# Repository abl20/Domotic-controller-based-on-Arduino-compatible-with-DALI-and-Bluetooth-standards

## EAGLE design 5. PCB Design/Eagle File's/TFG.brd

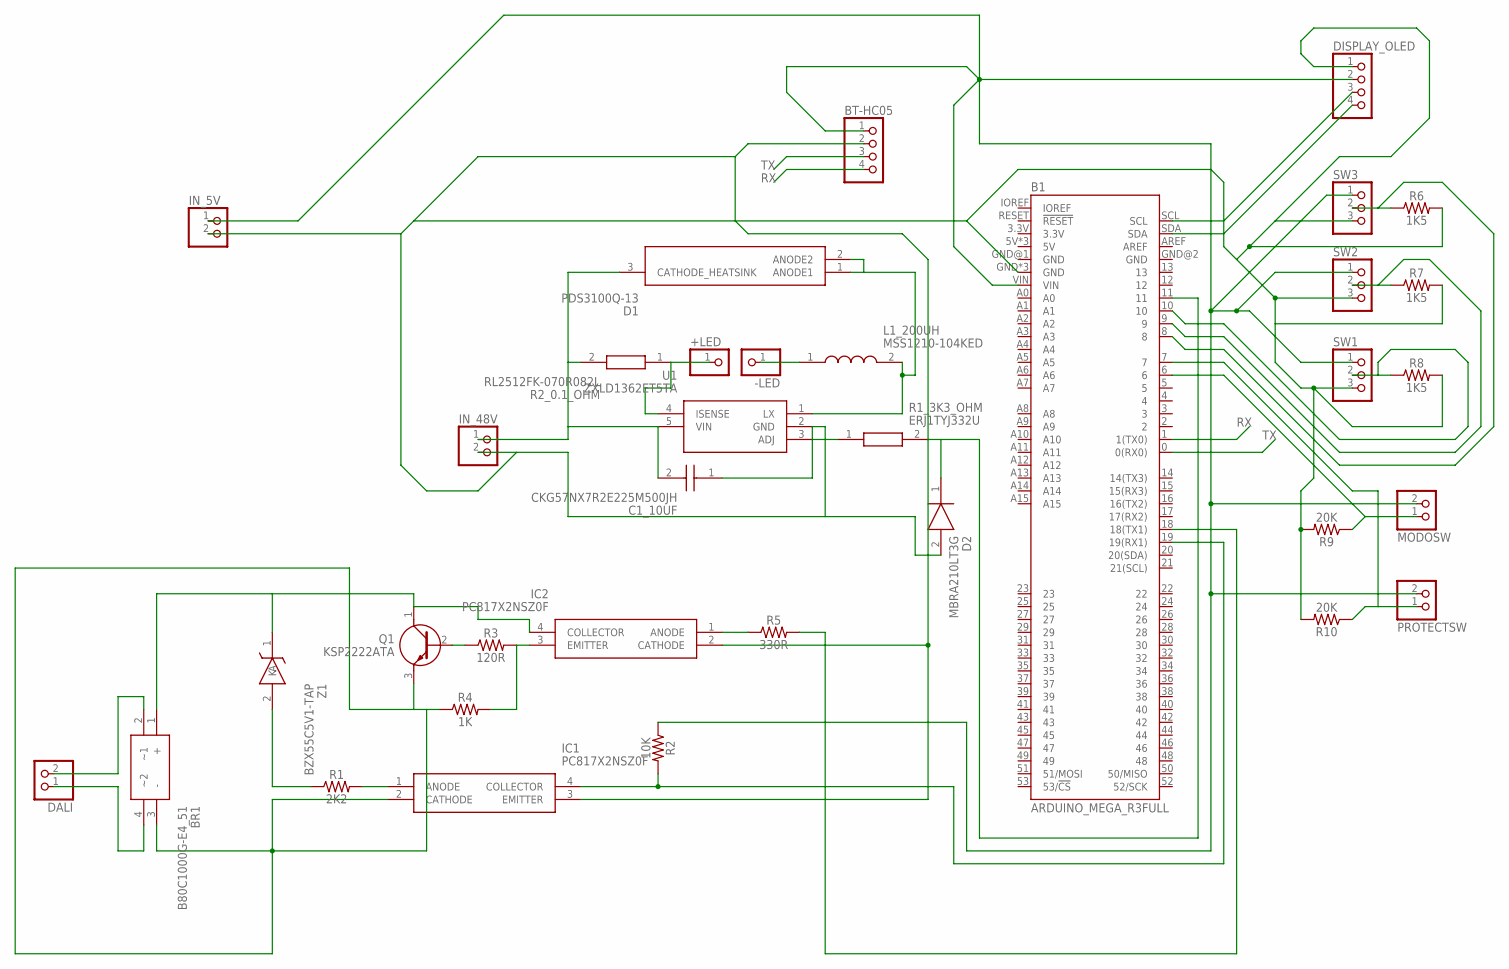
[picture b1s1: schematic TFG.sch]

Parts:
+LED: PINHD-1X1; 1X01
-LED: PINHD-1X1; 1X01
B1: ARDUINO_MEGA_R3FULL; ARDUINO_MEGA_NO_SILK
BR1: B80C1000G-E4_51; WOG_1
BT-HC05: PINHD-1X4; 1X04
C1_10UF: CKG57NX7R2E225M500JH; CAPC6050X550N
D1: PDS3100Q-13; POWERDI5
D2: MBRA210LT3G; DIOM5226X220N
DALI: PINHD-1X2; 1X02
DISPLAY_OLED: PINHD-1X4; 1X04
IC1, IC2: PC817X2NSZ0F; DIP762W60P254L458H400Q4N
IN_5V, IN_48V: PINHD-1X2; 1X02
L1_200UH: MSS1210-104KED; INDPM120120X1020N
MODOSW: PINHD-1X2; 1X02
PROTECTSW: PINHD-1X2; 1X02
Q1: KSP2222ATA; TO-92_FAIRCHILD
R1: 2K2; AXIAL-0.3
R1_3K3_OHM: ERJ1TYJ332U; RESC6432X70N
R2: 10K; AXIAL-0.3
R2_0.1_OHM: RL2512FK-070R082L; RESC6432X65N
R3: 120R; AXIAL-0.3
R4: 1K; AXIAL-0.3
R5: 330R; AXIAL-0.3
R6, R7, R8: 1K5; AXIAL-0.3
R9, R10: 20K; AXIAL-0.3
SW1, SW2, SW3: PINHD-1X3; 1X03
U1: ZXLD1362ET5TA; SOT95P270X145-5N
Z1: BZX55C5V1-TAP; DIOAD950W60L350D150

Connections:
2: C1_10UF.2, D1.3 (CATHODE_HEATSINK), IN_48V.1, R2_0.1_OHM.2, U1.5 (VIN)
unnamed: D1.1 (ANODE1), D1.2 (ANODE2), L1_200UH.2, U1.1 (LX)
unnamed: B1.GND, B1.GND@3 (GND), B1.GND@4 (GND), BT-HC05.2, C1_10UF.1, D2.2 (A), DISPLAY_OLED.1, IC1.3 (EMITTER), IC2.2 (CATHODE), IN_5V.2, IN_48V.2, R6.P$2 (2), R7.P$2 (2), R8.P$2 (2), R9.P$2 (2), R10.P$2 (2), SW1.3, SW2.3, SW3.3, U1.2 (GND)
unnamed: -LED.1, L1_200UH.1
unnamed: +LED.1, R2_0.1_OHM.1, U1.4 (ISENSE)
unnamed: B1.9, R7.P$1 (1), SW2.2
unnamed: B1.10, R8.P$1 (1), SW1.2
unnamed: B1.8, R6.P$1 (1), SW3.2
unnamed: R1_3K3_OHM.1, U1.3 (ADJ)
unnamed: B1.11, D2.1 (K), R1_3K3_OHM.2
unnamed: BR1.2 (~1), DALI.2
unnamed: BR1.4 (~2), DALI.1
unnamed: B1.6, MODOSW.1, R9.P$1 (1)
unnamed: BR1.1 (+), IC2.4 (COLLECTOR), Q1.1 (C), Z1.1 (K)
unnamed: R1.P$1 (1), Z1.2 (A)
unnamed: IC1.1 (ANODE), R1.P$2 (2)
unnamed: B1.19 (19(RX1)), IC1.4 (COLLECTOR), R2.P$2 (2)
unnamed: B1.VIN, BT-HC05.1, DISPLAY_OLED.2, IN_5V.1, MODOSW.2, PROTECTSW.2, R2.P$1 (1), SW1.1, SW2.1, SW3.1
unnamed: IC2.3 (EMITTER), R3.P$2 (2), R4.P$2 (2)
unnamed: Q1.2 (B), R3.P$1 (1)
unnamed: BR1.3 (-), IC1.2 (CATHODE), Q1.3 (E), R4.P$1 (1)
unnamed: B1.18 (18(TX1)), R5.P$2 (2)
unnamed: IC2.1 (ANODE), R5.P$1 (1)
unnamed: B1.7, PROTECTSW.1, R10.P$1 (1)
unnamed: B1.SCL, DISPLAY_OLED.3
unnamed: B1.SDA, DISPLAY_OLED.4
RX: B1.1 (1(TX0)), BT-HC05.4
TX: B1.0 (0(RX0)), BT-HC05.3

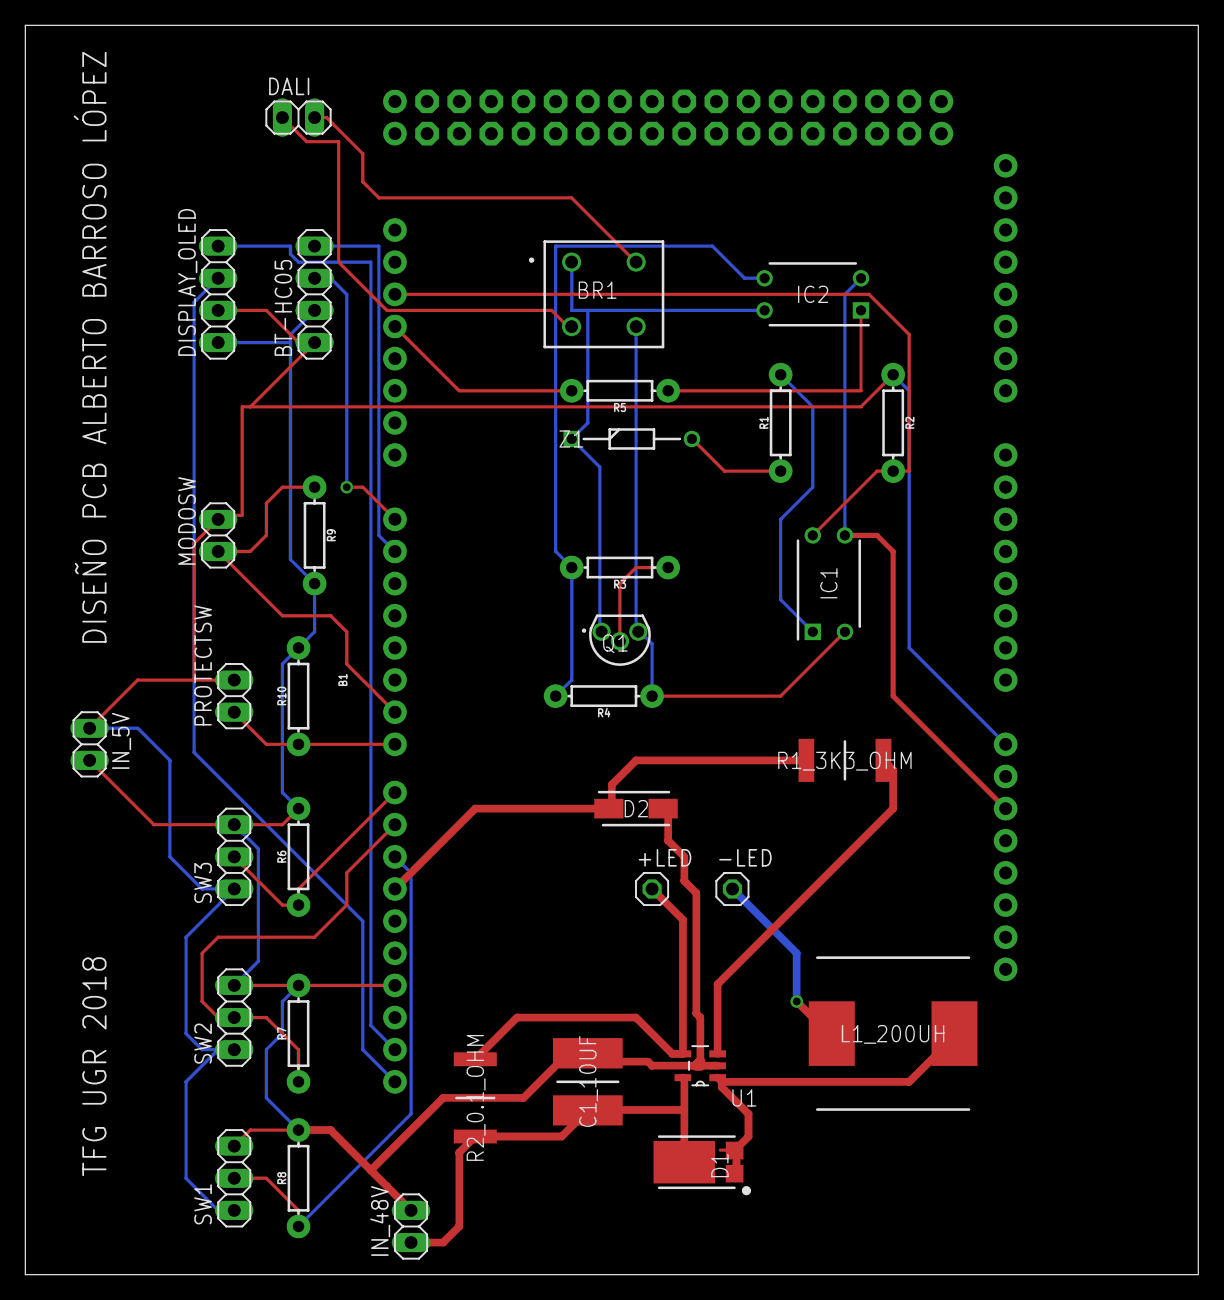
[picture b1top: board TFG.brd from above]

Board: 2 copper layers, 92.7 x 98.7 mm, 35 parts (0 on the bottom side), 28 nets.

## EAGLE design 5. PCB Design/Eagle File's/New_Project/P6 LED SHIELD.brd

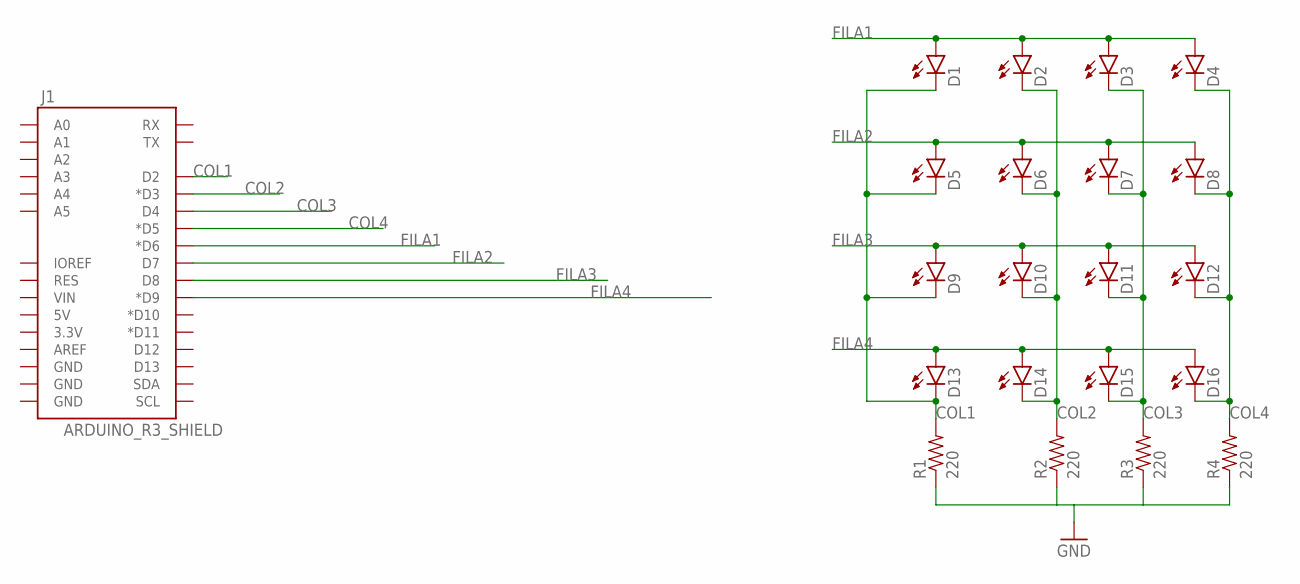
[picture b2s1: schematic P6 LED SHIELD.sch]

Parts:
D1, D2, D3, D4, D5, D6, D7, D8, D9, D10, D11, D12, D13, D14, D15, D16: LED5MM
J1: ARDUINO_R3_SHIELD; UNO_R3_SHIELD
R1, R2, R3, R4: 220; AXIAL-0.4

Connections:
COL1: D1.K (C), D5.K (C), D9.K (C), D13.K (C), J1.D2, R1.P$2 (2)
COL2: D2.K (C), D6.K (C), D10.K (C), D14.K (C), J1.D3 (*D3), R2.P$2 (2)
COL3: D3.K (C), D7.K (C), D11.K (C), D15.K (C), J1.D4, R3.P$2 (2)
COL4: D4.K (C), D8.K (C), D12.K (C), D16.K (C), J1.D5 (*D5), R4.P$2 (2)
FILA1: D1.A, D2.A, D3.A, D4.A, J1.D6 (*D6)
FILA2: D5.A, D6.A, D7.A, D8.A, J1.D7
FILA3: D9.A, D10.A, D11.A, D12.A, J1.D8
FILA4: D13.A, D14.A, D15.A, D16.A, J1.D9 (*D9)
GND: R1.P$1 (1), R2.P$1 (1), R3.P$1 (1), R4.P$1 (1)

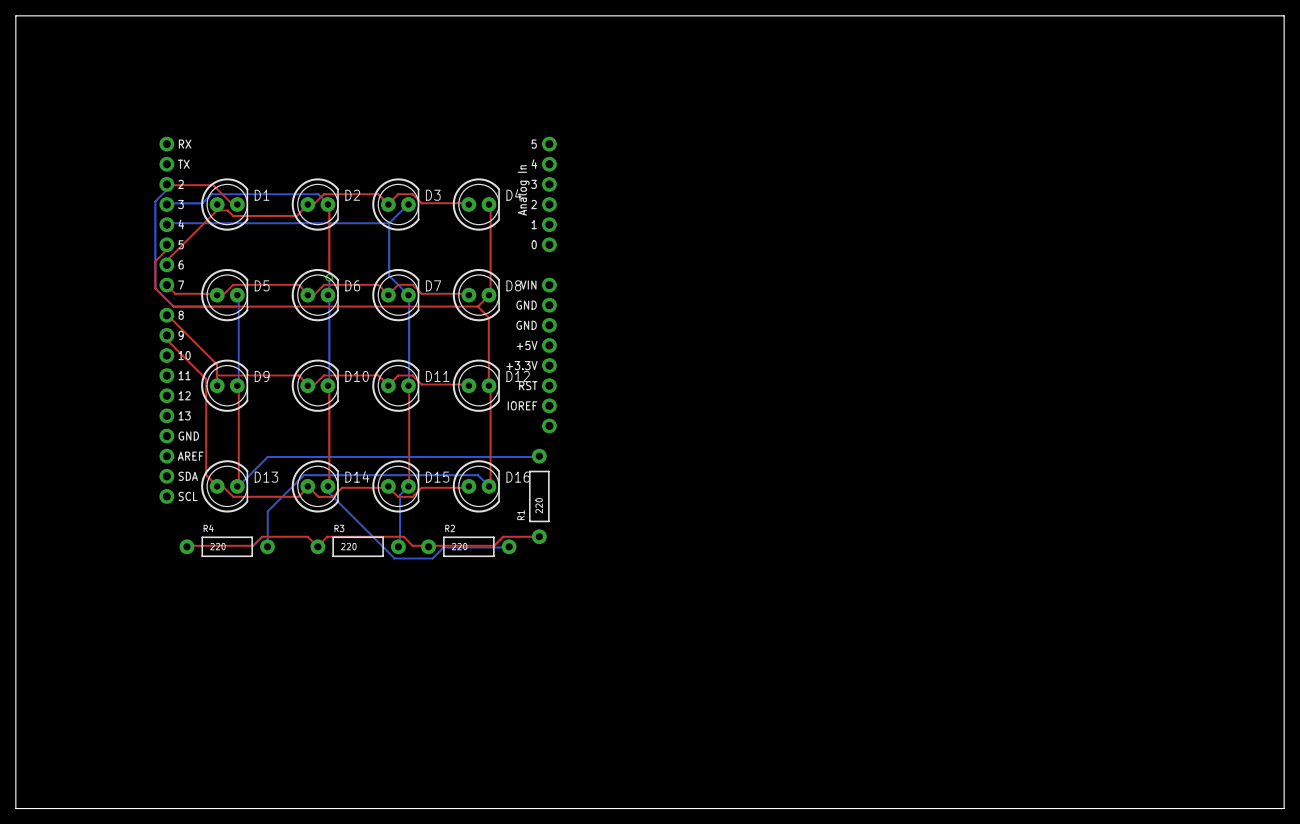
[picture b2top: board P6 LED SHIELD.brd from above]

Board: 2 copper layers, 160.0 x 100.0 mm, 21 parts (0 on the bottom side), 9 nets.

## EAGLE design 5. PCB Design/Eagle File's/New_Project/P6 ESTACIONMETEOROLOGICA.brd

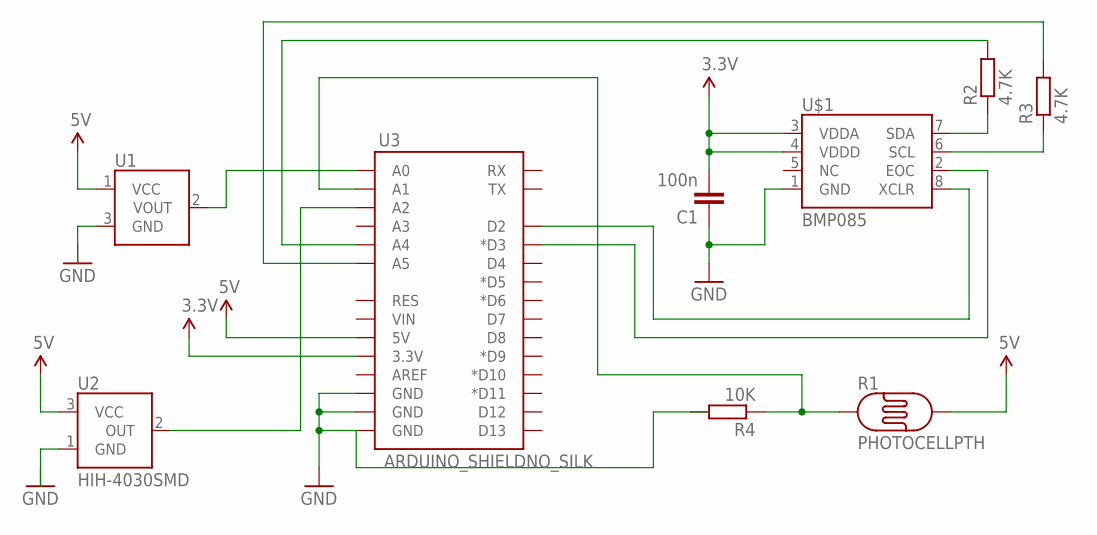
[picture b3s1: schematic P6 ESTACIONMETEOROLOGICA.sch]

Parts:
C1: 100n; C0805
R1: PHOTOCELLPTH; PHOTOCELL
R2, R3: 4.7K; R0805
R4: 10K; R0805
U1: TMP36GT9; TO-92
U2: HIH-4030SMD; HIH-4030
U3: ARDUINO_SHIELDNO_SILK; DUEMILANOVE_VIAS
U$1: BMP085

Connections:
3.3V: C1.2, U3.3.3V, U$1.3 (VDDA), U$1.4 (VDDD)
5V: R1.2, U1.1 (VCC), U2.3 (VCC), U3.5V
GND: C1.1, U3.GND@0 (GND), U3.GND@1 (GND), U3.GND@2 (GND), U$1.1 (GND)
unnamed: R2.1, U$1.7 (SDA)
unnamed: R2.2, U3.A4
unnamed: R3.1, U$1.6 (SCL)
unnamed: R3.2, U3.A5
unnamed: U3.D2, U$1.8 (XCLR)
unnamed: U3.D3 (*D3), U$1.2 (EOC)
unnamed: R1.1, R4.1, U3.A1
unnamed: U2.2 (OUT), U3.A2
unnamed: U1.2 (VOUT), U3.A0

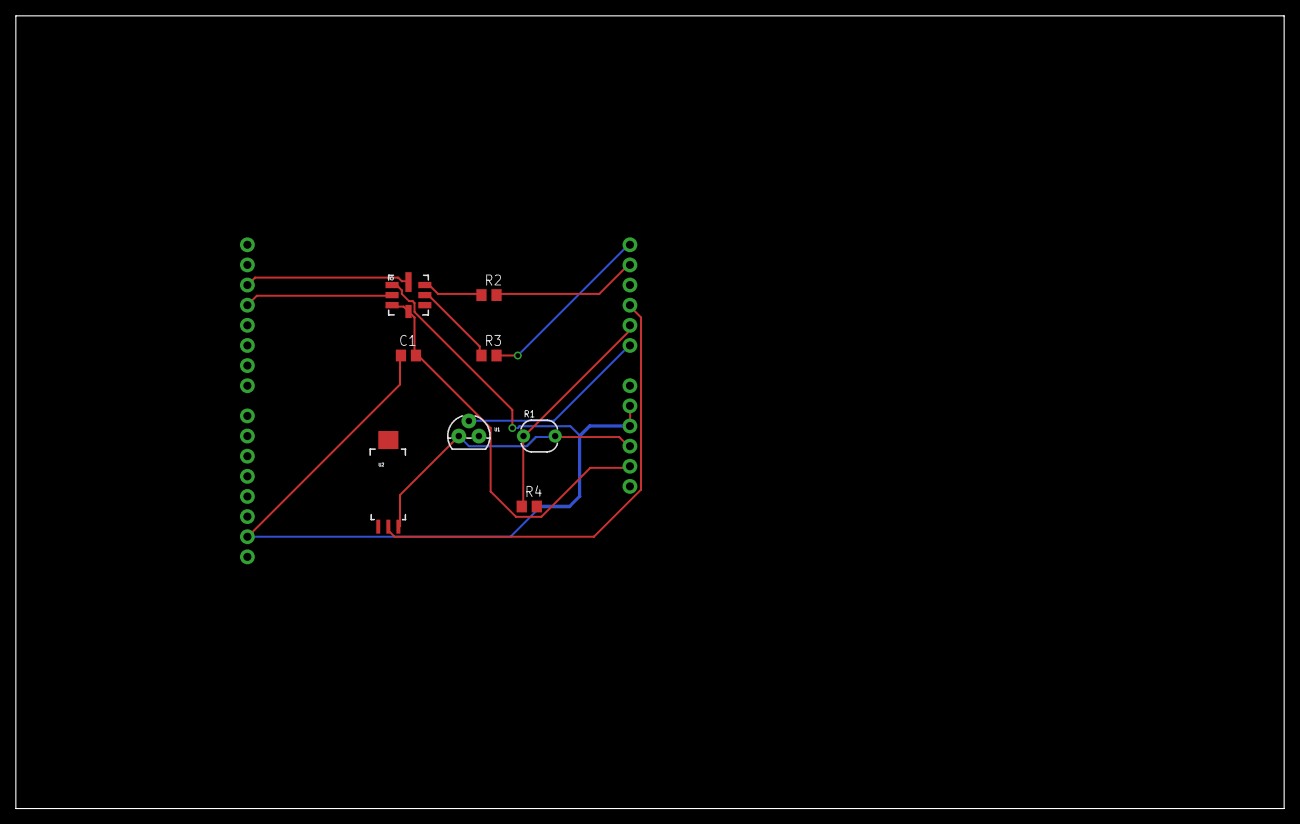
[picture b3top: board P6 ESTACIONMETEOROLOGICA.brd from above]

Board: 2 copper layers, 160.0 x 100.0 mm, 9 parts (0 on the bottom side), 12 nets.

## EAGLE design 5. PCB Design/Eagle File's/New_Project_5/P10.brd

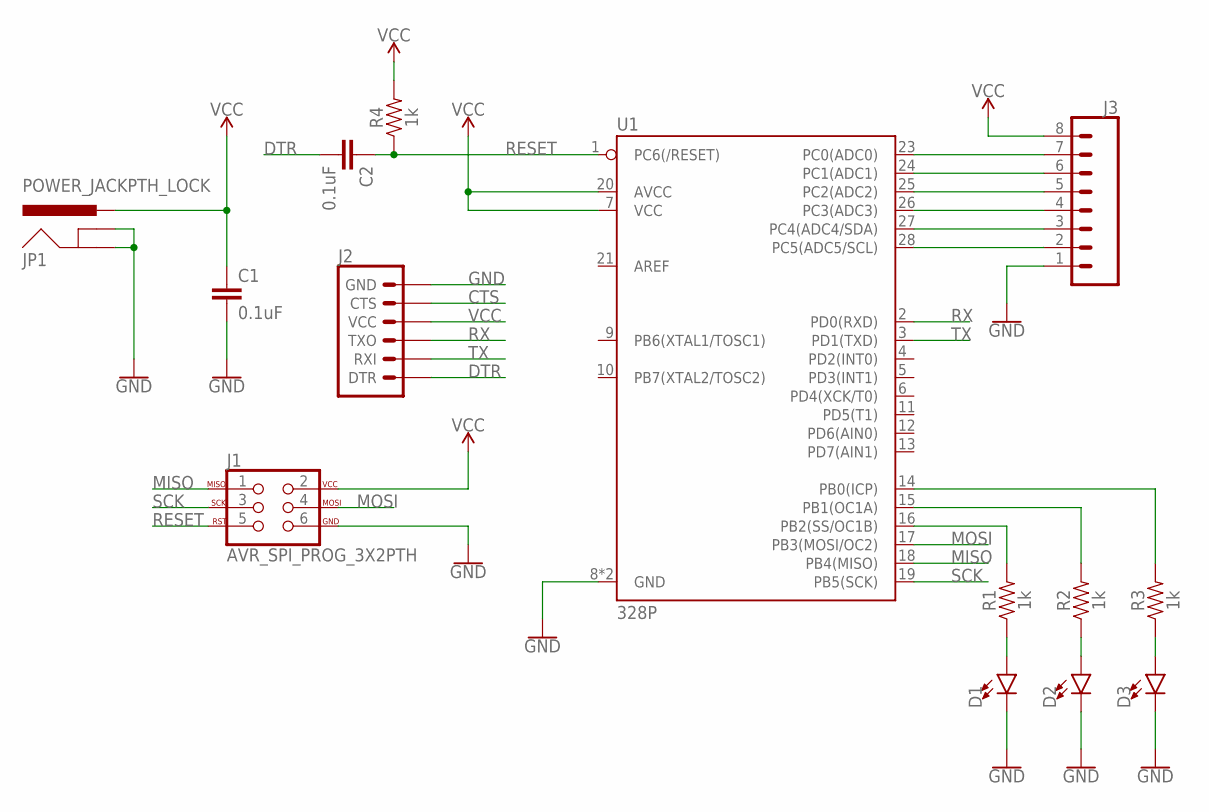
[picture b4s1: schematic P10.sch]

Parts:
C1, C2: 0.1uF; CAP-PTH-SMALL
D1, D2, D3: LED5MM; LED_5MM
J1: AVR_SPI_PROG_3X2PTH; 2X3
J2: 6_PIN_SERIAL_TARGET; 1X06
J3: CONN_08"; 1X08
JP1: POWER_JACKPTH_LOCK; POWER_JACK_PTH_LOCK
R1, R2, R3, R4: 1k; AXIAL-0.3
U1: 328P; DIP28

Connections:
CTS: J2.5 (CTS)
DTR: C2.2, J2.1 (DTR)
GND: C1.2, D1.K (C), D2.K (C), D3.K (C), J1.6, J2.6 (GND), J3.1, JP1.GND, JP1.GNDBREAK, U1.8 (GND), U1.22 (GND)
MISO: J1.1, U1.18 (PB4(MISO))
MOSI: J1.4, U1.17 (PB3(MOSI/OC2))
unnamed: J3.7, U1.23 (PC0(ADC0))
unnamed: J3.6, U1.24 (PC1(ADC1))
unnamed: J3.5, U1.25 (PC2(ADC2))
unnamed: J3.4, U1.26 (PC3(ADC3))
unnamed: J3.3, U1.27 (PC4(ADC4/SDA))
unnamed: J3.2, U1.28 (PC5(ADC5/SCL))
unnamed: R1.P$2 (2), U1.16 (PB2(SS/OC1B))
unnamed: R2.P$2 (2), U1.15 (PB1(OC1A))
unnamed: R3.P$2 (2), U1.14 (PB0(ICP))
unnamed: D1.A, R1.P$1 (1)
unnamed: D2.A, R2.P$1 (1)
unnamed: D3.A, R3.P$1 (1)
RESET: C2.1, J1.5, R4.P$1 (1), U1.1 (PC6(/RESET))
RX: J2.3 (TXO), U1.2 (PD0(RXD))
SCK: J1.3, U1.19 (PB5(SCK))
TX: J2.2 (RXI), U1.3 (PD1(TXD))
VCC: C1.1, J1.2, J2.4 (VCC), J3.8, JP1.PWR, R4.P$2 (2), U1.7 (VCC), U1.20 (AVCC)

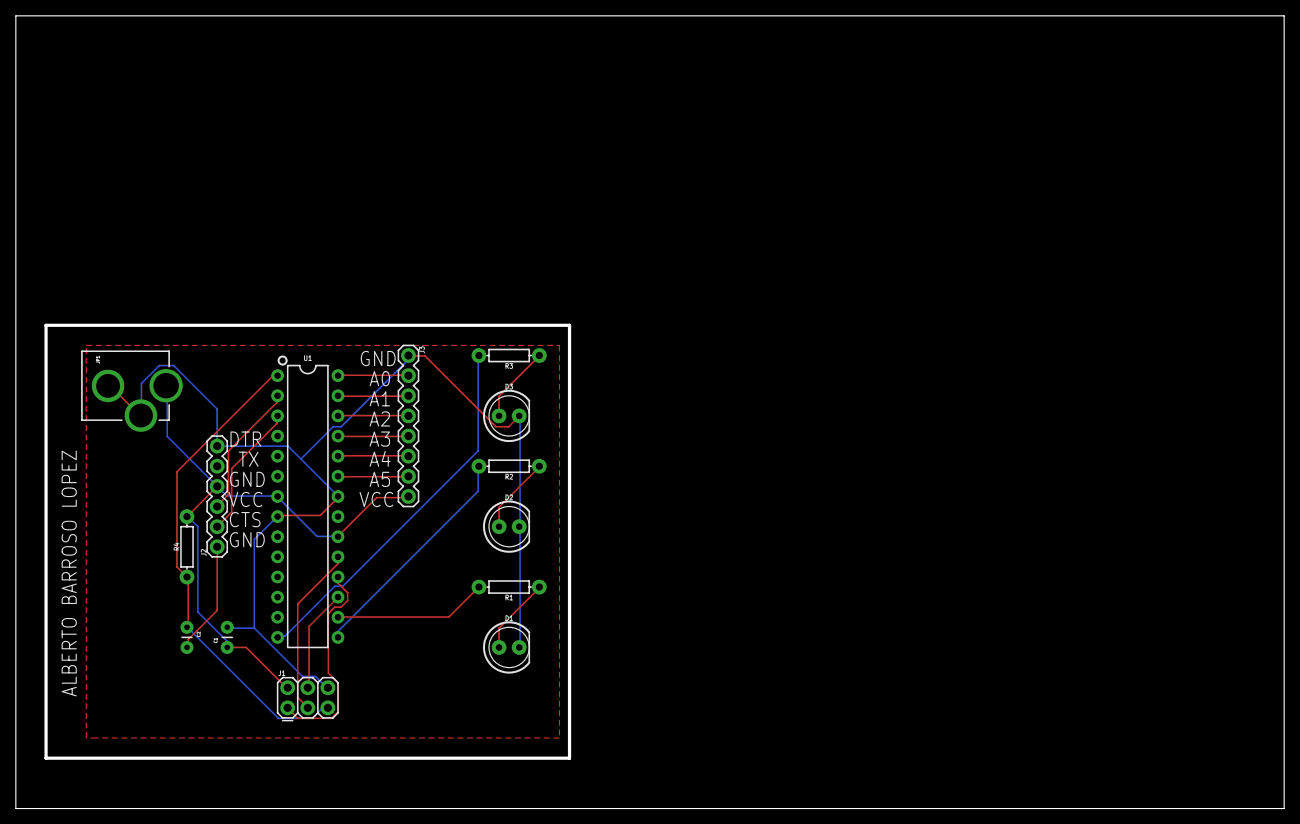
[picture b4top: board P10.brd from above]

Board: 2 copper layers, 160.0 x 100.0 mm, 14 parts (0 on the bottom side), 21 nets.

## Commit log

2018-12-06 Domotic controller compatible with DALI and Bluetooth

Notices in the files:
parts and their libraries:
SparkFun-Sensors: Licensing: Creative Commons ShareAlike 4.0 International - https://creativecommons.org/licenses/by-sa/4.0
